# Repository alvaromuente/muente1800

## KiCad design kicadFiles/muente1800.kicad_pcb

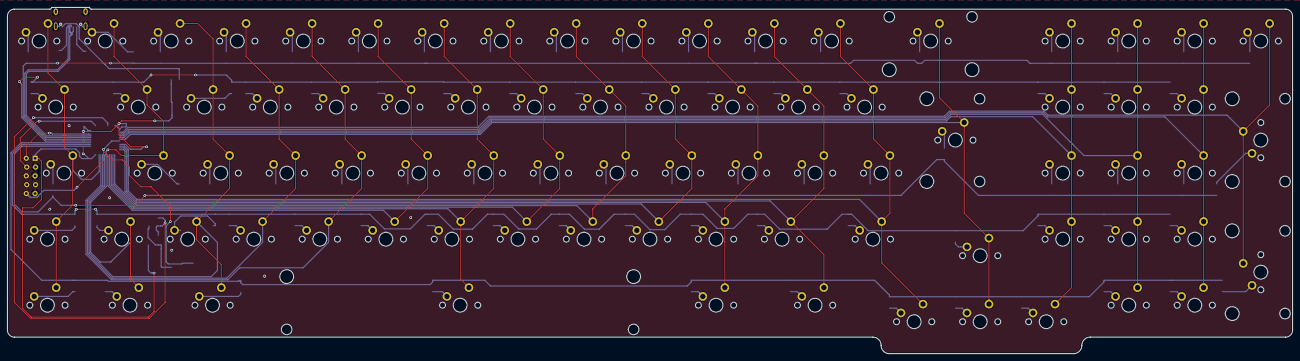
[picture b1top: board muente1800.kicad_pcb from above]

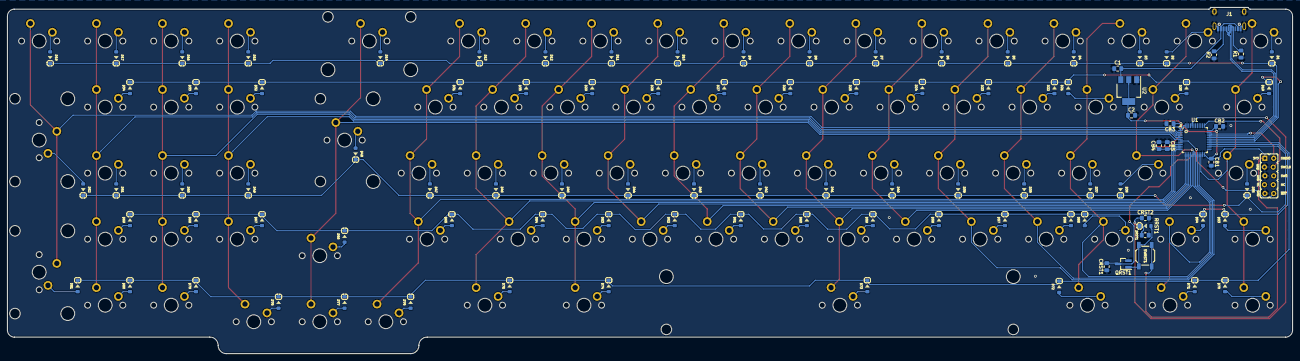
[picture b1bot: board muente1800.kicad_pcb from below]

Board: 2 copper layers, 370.7 x 99.9 mm, 181 parts (181 on the bottom side), 116 nets.

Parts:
C1: 100nF; C_0805_2012Metric_Pad1.15x1.40mm_HandSolder
C2: 10uF; C_0805_2012Metric_Pad1.15x1.40mm_HandSolder
CB1, CB2, CB3, CB4: 100nF; C_0805_2012Metric_Pad1.15x1.40mm_HandSolder
CB5: 10nF; C_0805_2012Metric_Pad1.15x1.40mm_HandSolder
CRST1: 4.7nF; C_0805_2012Metric_Pad1.15x1.40mm_HandSolder
CRST2: 10uF; C_0805_2012Metric_Pad1.15x1.40mm_HandSolder
D1, D2, D3, D4, D5, D6, D7, D8, D9, D10, D11, D12, D13, D14, D15, D16, D17, D18, D19, D20, D21, D22, D23, D24, D25, D26, D27, D28, D29, D30, D31, D32, D33, D34, D35, D36, D37, D38, D39, D40, D41, D42, D43, D44, D45, D46, D47, D48, D49, D50, D51, D52, D53, D54, D55, D56, D57, D58, D59, D60, D61, D62, D63, D64, D65, D66, D67, D68, D69, D70, D71, D72, D73, D74, D75, D76, D77, D78, D79, D80, D81: 1N4148; D_SOD-123
DRST1: 1N4148; D_SOD-123
J1: TYPE-C-31-M12_13; TYPE-C-31-M-12
J2: Conn_01x14; Conn_ARM_JTAG_SWD_10
QRST1: DTC123J; SOT-23_Handsoldering
R1, R2: 5.1k; R_0805_2012Metric_Pad1.15x1.40mm_HandSolder
RRST1: 100k; R_0805_2012Metric_Pad1.15x1.40mm_HandSolder
SW1, SW2, SW3, SW4, SW5, SW6, SW7, SW8, SW9, SW10, SW11, SW12, SW13, SW15, SW16, SW17, SW18, SW20, SW21, SW22, SW23, SW24, SW25, SW26, SW27, SW28, SW29, SW30, SW31, SW32, SW33, SW34, SW36, SW37, SW38, SW39, SW40, SW41, SW42, SW43, SW44, SW45, SW46, SW47, SW49, SW50, SW51, SW54, SW55, SW56, SW57, SW58, SW59, SW60, SW61, SW62, SW63, SW64, SW66, SW67, SW68, SW69, SW76, SW77, SW78, SW79, SW80: MXSwitch_100; MX100
SW14: MXSwitch_200; MX200
SW19, SW74, SW75: MXSwitch_150; MX150
SW35, SW65: MXSwitch_175; MX175
SW48: MXSwitch_ISO; MX_ISOEnter
SW52, SW81: MXSwitch_200; MX200R
SW53, SW70, SW71, SW72: MXSwitch_125; MX125
SW73: MXSwitch_625; MX625R
SWRST1: SW_Push; K2-1187SQ-A4SW-06
U1: STM32F072CBTx; LQFP-48_7x7mm_P0.5mm
U2: LD1117S33TR_SOT223; SOT-223-3_TabPin2

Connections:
+3V3: C2.1, CB1.1, CB2.1, CB3.1, CB4.1, CB5.1, J2.1, SWRST1.1, U1.1, U1.9, U1.24, U1.36, U1.48, U2.2
BOOT0: CRST2.1, DRST1.1, RRST1.1, U1.44
D+: J1.A6, J1.B6, U1.33
D-: J1.A7, J1.B7, U1.32
GND: C1.2, C2.2, CB1.2, CB2.2, CB3.2, CB4.2, CB5.2, CRST1.1, CRST2.2, J1.A1, J1.B1, J1.S, J2.3, J2.5, J2.9, QRST1.2, R1.1, R2.1, RRST1.2, U1.8, U1.23, U1.35, U1.47, U2.1
NRST: CRST1.2, J2.10, QRST1.3, U1.7
unnamed: D1.2, SW1.2
unnamed: D2.2, SW2.2
unnamed: D3.2, SW3.2
unnamed: D4.2, SW4.2
unnamed: D5.2, SW5.2
unnamed: D6.2, SW6.2
unnamed: D7.2, SW7.2
unnamed: D8.2, SW8.2
unnamed: D9.2, SW9.2
unnamed: D10.2, SW10.2
unnamed: D11.2, SW11.2
unnamed: D12.2, SW12.2
unnamed: D13.2, SW13.2
unnamed: D14.2, SW14.2
unnamed: D15.2, SW15.2
unnamed: D16.2, SW16.2
unnamed: D17.2, SW17.2
unnamed: D18.2, SW18.2
unnamed: D19.2, SW19.2
unnamed: D20.2, SW20.2
unnamed: D21.2, SW21.2
unnamed: D22.2, SW22.2
unnamed: D23.2, SW23.2
unnamed: D24.2, SW24.2
unnamed: D25.2, SW25.2
unnamed: D26.2, SW26.2
unnamed: D27.2, SW27.2
unnamed: D28.2, SW28.2
unnamed: D29.2, SW29.2
unnamed: D30.2, SW30.2
unnamed: D31.2, SW31.2
unnamed: D32.2, SW32.2
unnamed: D33.2, SW33.2
unnamed: D34.2, SW34.2
unnamed: D35.2, SW35.2
unnamed: D36.2, SW36.2
unnamed: D37.2, SW37.2
unnamed: D38.2, SW38.2
unnamed: D39.2, SW39.2
unnamed: D40.2, SW40.2
unnamed: D41.2, SW41.2
unnamed: D42.2, SW42.2
unnamed: D43.2, SW43.2
unnamed: D44.2, SW44.2
unnamed: D45.2, SW45.2
unnamed: D46.2, SW46.2
unnamed: D47.2, SW47.2
unnamed: D48.2, SW48.2
unnamed: D49.2, SW49.2
unnamed: D50.2, SW50.2
unnamed: D51.2, SW51.2
unnamed: D52.2, SW52.2
unnamed: D53.2, SW53.2
unnamed: D54.2, SW54.2
unnamed: D55.2, SW55.2
unnamed: D56.2, SW56.2
unnamed: D57.2, SW57.2
unnamed: D58.2, SW58.2
unnamed: D59.2, SW59.2
unnamed: D60.2, SW60.2
unnamed: D61.2, SW61.2
unnamed: D62.2, SW62.2
unnamed: D63.2, SW63.2
unnamed: D64.2, SW64.2
unnamed: D65.2, SW65.2
unnamed: D66.2, SW66.2
unnamed: D67.2, SW67.2
unnamed: D68.2, SW68.2
unnamed: D69.2, SW69.2
unnamed: D70.2, SW70.2
unnamed: D71.2, SW71.2
unnamed: D72.2, SW72.2
unnamed: D73.2, SW73.2
unnamed: D74.2, SW74.2
unnamed: D75.2, SW75.2
unnamed: D76.2, SW76.2
unnamed: D77.2, SW77.2
unnamed: D78.2, SW78.2
unnamed: D79.2, SW79.2
unnamed: D80.2, SW80.2
unnamed: D81.2, SW81.2
unnamed: DRST1.2, QRST1.1, SWRST1.2
unnamed: J1.A5, R1.2
unnamed: J1.B5, R2.2
SWCLK: J2.4, U1.37
SWDIO: J2.2, U1.34
VBUS: C1.1, J1.A4, J1.B4, U2.3
col0: SW1.1, SW19.1, SW35.1, SW53.1, SW70.1, U1.22
col1: SW2.1, SW20.1, SW36.1, SW54.1, SW71.1, U1.18
col2: SW3.1, SW21.1, SW37.1, SW55.1, SW72.1, U1.19
col3: SW4.1, SW22.1, SW38.1, SW56.1, U1.20
col4: SW5.1, SW23.1, SW39.1, SW57.1, U1.21
col5: SW6.1, SW24.1, SW40.1, SW58.1, U1.17
col6: SW7.1, SW25.1, SW41.1, SW59.1, SW73.1, U1.16
col7: SW8.1, SW26.1, SW42.1, SW60.1, U1.15
col8: SW9.1, SW27.1, SW43.1, SW61.1, U1.14
col9: SW10.1, SW28.1, SW44.1, SW62.1, U1.13
col10: SW11.1, SW29.1, SW45.1, SW63.1, SW74.1, U1.12
col11: SW12.1, SW30.1, SW46.1, SW64.1, SW75.1, U1.11
col12: SW13.1, SW31.1, SW47.1, SW65.1, SW76.1, U1.10
col13: SW14.1, SW48.1, SW66.1, SW77.1, U1.6
col14: SW15.1, SW32.1, SW49.1, SW67.1, SW78.1, U1.5
col15: SW16.1, SW33.1, SW50.1, SW68.1, SW79.1, U1.4
col16: SW17.1, SW34.1, SW51.1, SW69.1, SW80.1, U1.3
col17: SW18.1, SW52.1, SW81.1, U1.2
row0: D1.1, D2.1, D3.1, D4.1, D5.1, D6.1, D7.1, D8.1, D9.1, D10.1, D11.1, D12.1, D13.1, D14.1, D15.1, D16.1, D17.1, D18.1, U1.31
row1: D19.1, D20.1, D21.1, D22.1, D23.1, D24.1, D25.1, D26.1, D27.1, D28.1, D29.1, D30.1, D31.1, D32.1, D33.1, D34.1, U1.30
row2: D35.1, D36.1, D37.1, D38.1, D39.1, D40.1, D41.1, D42.1, D43.1, D44.1, D45.1, D46.1, D47.1, D48.1, D49.1, D50.1, D51.1, D52.1, U1.27
row3: D53.1, D54.1, D55.1, D56.1, D57.1, D58.1, D59.1, D60.1, D61.1, D62.1, D63.1, D64.1, D65.1, D66.1, D67.1, D68.1, D69.1, U1.28
row4: D70.1, D71.1, D72.1, D73.1, D74.1, D75.1, D76.1, D77.1, D78.1, D79.1, D80.1, D81.1, U1.29

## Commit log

2020-02-19 switch matrix
2020-02-19 switches
2020-02-19 edge cut
2020-02-19 edge cuts
2020-02-19 ground fill
2020-02-19 sch done
2020-02-27 routing
2020-02-27 finished routing
2020-02-27 added pcb renders
